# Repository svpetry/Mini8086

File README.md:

# Mini8086
A small, extensible Intel 8086 based computer system.

## PCBs

Some boards are made with Eagle but then I switched to KiCad because my Eagle License covers only 2 layer boards and I don't like their new licensing model (it's too expensive for hobbyists).
Schematics and layout are contained in the folders Eagle and KiCad.

### Backplane (Eagle)

First revision of the system backplane with 6 slots and a power connector.

### Backplane (KiCad)

Second revision of the backplane. Has 7 slots and two power connectors (one of them USB-C).

### RAM board (Eagle)

RAM board with 512 KB SRAM.

### Info board (KiCad)

A 16x2 HD44780 based LCD can be mounted to this board. Also contains some LEDs for important signals.

### LED board (KiCad)

Information board with LEDs for the busses and all important signals.

### CPU board Rev 1 (KiCad, "main") 

First revision of the CPU board, contains socket for an Intel 8086 CPU, ROM and other important system chips:
* Intel 8259 interrupt controller
* Intel 8254 timer

### CPU board Rev 2 (KiCad, "mainv2")

Second revision of the CPU board where I replaced most of the logic chips with an Altera CPLD. Also contains 1 MB SRAM so the external RAM board is not needed.

### VGA board (KiCad)

Simple graphics card with 128 KB SRAM and VGA output. Supported modes:
* text mode 80x25 characters, 256 colors (resolution 640x400 pixels)
* 320x200, 256 colors
* 320x400, 256 colors
* 640x200, 256 colors

### I/O board (KiCad)

* Slots for SD and MicroSD cards. Simple SPI controller implemented in an Altera CPLD.
* PS/2 keyboard connector
* RS232 connector
* I²C controller with a RTC module, BMP sensor module and EEPROM connected.

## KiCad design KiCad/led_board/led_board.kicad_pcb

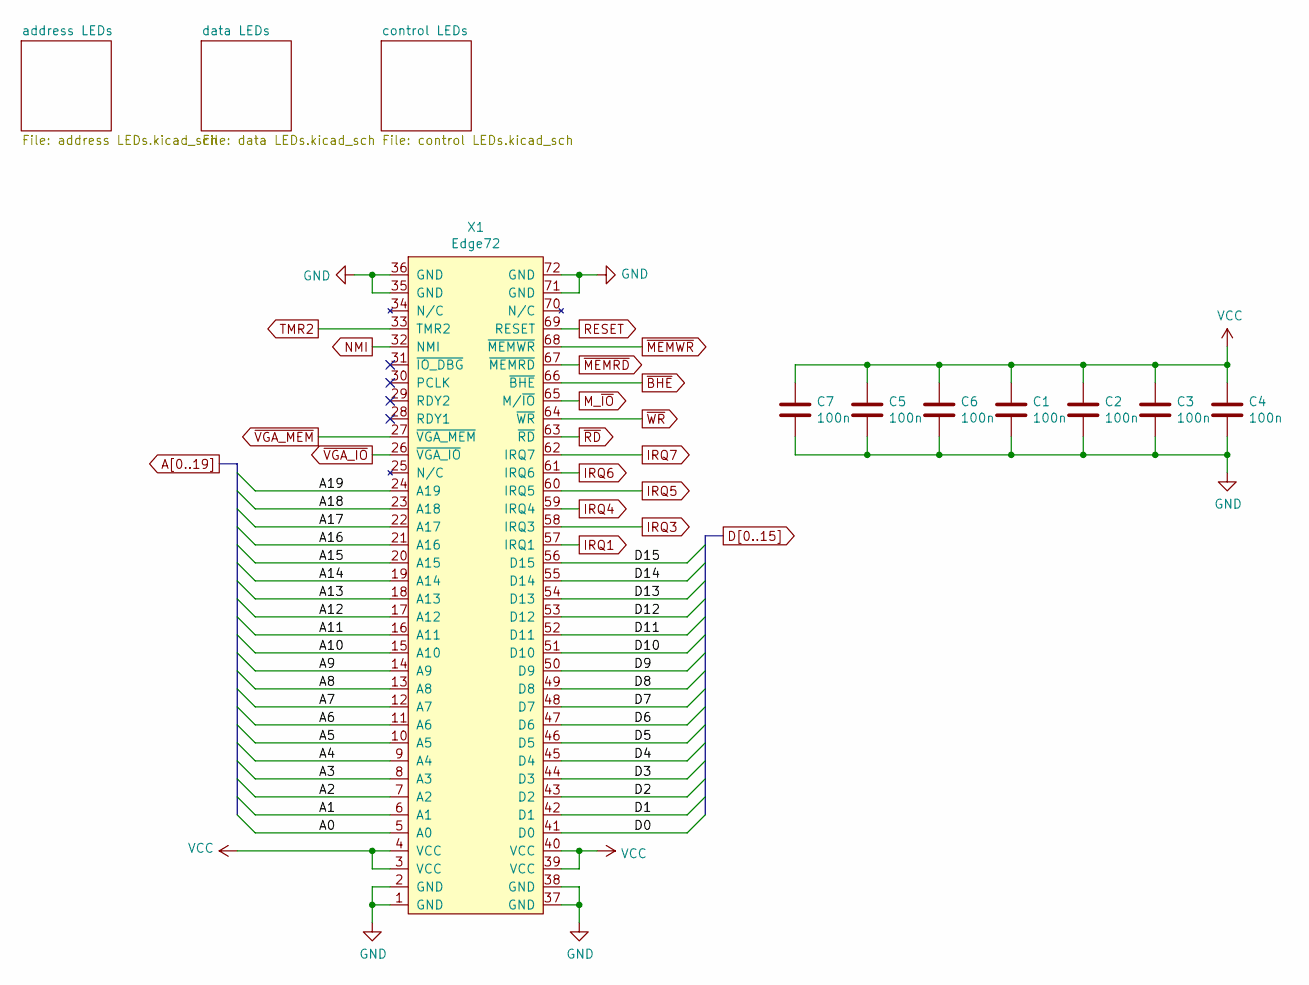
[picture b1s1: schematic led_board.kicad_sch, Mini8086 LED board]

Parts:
C1, C2, C3, C4, C5, C6, C7: 100n; C_1206_3216Metric; LCSC C24497
X1: Edge72; BUS_72

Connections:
A0: X1.5 (A0); also elsewhere on the board
A1: X1.6 (A1); also elsewhere on the board
A2: X1.7 (A2); also elsewhere on the board
A3: X1.8 (A3); also elsewhere on the board
A4: X1.9 (A4); also elsewhere on the board
A5: X1.10 (A5); also elsewhere on the board
A6: X1.11 (A6); also elsewhere on the board
A7: X1.12 (A7); also elsewhere on the board
A8: X1.13 (A8); also elsewhere on the board
A9: X1.14 (A9); also elsewhere on the board
A10: X1.15 (A10); also elsewhere on the board
A11: X1.16 (A11); also elsewhere on the board
A12: X1.17 (A12); also elsewhere on the board
A13: X1.18 (A13); also elsewhere on the board
A14: X1.19 (A14); also elsewhere on the board
A15: X1.20 (A15); also elsewhere on the board
A16: X1.21 (A16); also elsewhere on the board
A17: X1.22 (A17); also elsewhere on the board
A18: X1.23 (A18); also elsewhere on the board
A19: X1.24 (A19); also elsewhere on the board
D0: X1.41 (D0); also elsewhere on the board
D1: X1.42 (D1); also elsewhere on the board
D2: X1.43 (D2); also elsewhere on the board
D3: X1.44 (D3); also elsewhere on the board
D4: X1.45 (D4); also elsewhere on the board
D5: X1.46 (D5); also elsewhere on the board
D6: X1.47 (D6); also elsewhere on the board
D7: X1.48 (D7); also elsewhere on the board
D8: X1.49 (D8); also elsewhere on the board
D9: X1.50 (D9); also elsewhere on the board
D10: X1.51 (D10); also elsewhere on the board
D11: X1.52 (D11); also elsewhere on the board
D12: X1.53 (D12); also elsewhere on the board
D13: X1.54 (D13); also elsewhere on the board
D14: X1.55 (D14); also elsewhere on the board
D15: X1.56 (D15); also elsewhere on the board
GND: C1.2, C2.2, C3.2, C4.2, C5.2, C6.2, C7.2, X1.1 (GND), X1.2 (GND), X1.35 (GND), X1.36 (GND), X1.37 (GND), X1.38 (GND), X1.71 (GND), X1.72 (GND); also elsewhere on the board
IRQ1: X1.57 (IRQ1); also elsewhere on the board
IRQ3: X1.58 (IRQ3); also elsewhere on the board
IRQ4: X1.59 (IRQ4); also elsewhere on the board
IRQ5: X1.60 (IRQ5); also elsewhere on the board
IRQ6: X1.61 (IRQ6); also elsewhere on the board
IRQ7: X1.62 (IRQ7); also elsewhere on the board
M_~IO: X1.65 (M/~IO); also elsewhere on the board
NMI: X1.32 (NMI); also elsewhere on the board
RESET: X1.69 (RESET); also elsewhere on the board
TMR2: X1.33 (TMR2); also elsewhere on the board
VCC: C1.1, C2.1, C3.1, C4.1, C5.1, C6.1, C7.1, X1.3 (VCC), X1.4 (VCC), X1.39 (VCC), X1.40 (VCC); also elsewhere on the board
~BHE: X1.66 (~BHE); also elsewhere on the board
~MEMRD: X1.67 (~MEMRD); also elsewhere on the board
~MEMWR: X1.68 (~MEMWR); also elsewhere on the board
~RD: X1.63 (~RD); also elsewhere on the board
~VGA_IO: X1.26 (~VGA_IO); also elsewhere on the board
~VGA_MEM: X1.27 (~VGA_MEM); also elsewhere on the board
~WR: X1.64 (~WR); also elsewhere on the board

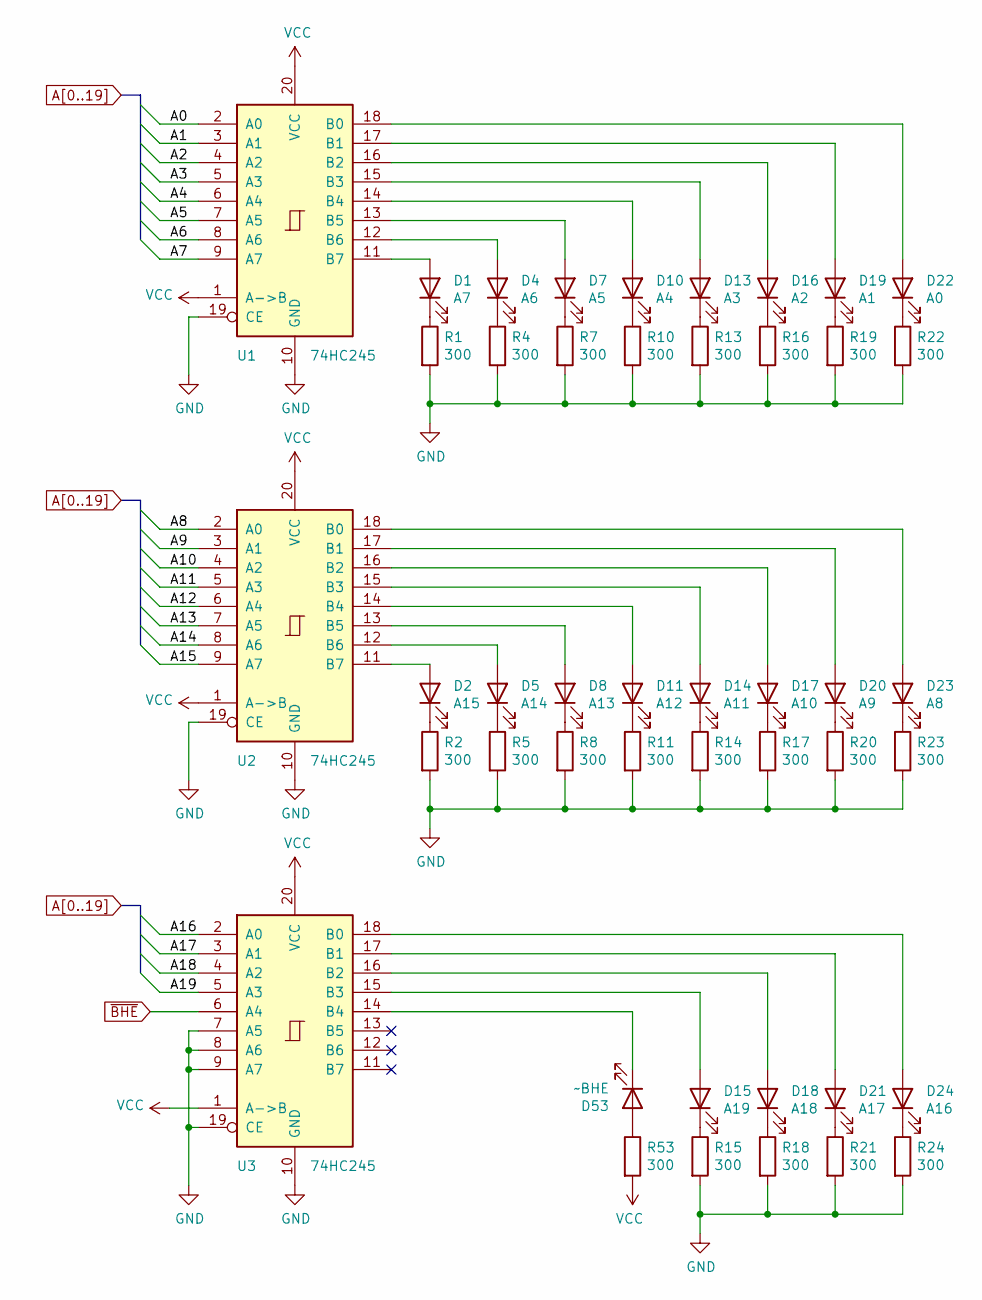
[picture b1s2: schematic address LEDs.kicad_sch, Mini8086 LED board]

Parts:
D1: A7; LED_0603_1608Metric
D2: A15; LED_0603_1608Metric
D4: A6; LED_0603_1608Metric
D5: A14; LED_0603_1608Metric
D7: A5; LED_0603_1608Metric
D8: A13; LED_0603_1608Metric
D10: A4; LED_0603_1608Metric
D11: A12; LED_0603_1608Metric
D13: A3; LED_0603_1608Metric
D14: A11; LED_0603_1608Metric
D15: A19; LED_0603_1608Metric
D16: A2; LED_0603_1608Metric
D17: A10; LED_0603_1608Metric
D18: A18; LED_0603_1608Metric
D19: A1; LED_0603_1608Metric
D20: A9; LED_0603_1608Metric
D21: A17; LED_0603_1608Metric
D22: A0; LED_0603_1608Metric
D23: A8; LED_0603_1608Metric
D24: A16; LED_0603_1608Metric
D53: ~BHE; LED_0603_1608Metric
R1, R2, R4, R5, R7, R8, R10, R11, R13, R14, R15, R16, R17, R18, R19, R20, R21, R22, R23, R24, R53: 300; R_1206_3216Metric
U1, U2, U3: 74HC245; SO-20_12.8x7.5mm_P1.27mm; LCSC C5625

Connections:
A0: U1.2 (A0); also elsewhere on the board
A1: U1.3 (A1); also elsewhere on the board
A2: U1.4 (A2); also elsewhere on the board
A3: U1.5 (A3); also elsewhere on the board
A4: U1.6 (A4); also elsewhere on the board
A5: U1.7 (A5); also elsewhere on the board
A6: U1.8 (A6); also elsewhere on the board
A7: U1.9 (A7); also elsewhere on the board
A8: U2.2 (A0); also elsewhere on the board
A9: U2.3 (A1); also elsewhere on the board
A10: U2.4 (A2); also elsewhere on the board
A11: U2.5 (A3); also elsewhere on the board
A12: U2.6 (A4); also elsewhere on the board
A13: U2.7 (A5); also elsewhere on the board
A14: U2.8 (A6); also elsewhere on the board
A15: U2.9 (A7); also elsewhere on the board
A16: U3.2 (A0); also elsewhere on the board
A17: U3.3 (A1); also elsewhere on the board
A18: U3.4 (A2); also elsewhere on the board
A19: U3.5 (A3); also elsewhere on the board
GND: R1.2, R2.2, R4.2, R5.2, R7.2, R8.2, R10.2, R11.2, R13.2, R14.2, R15.2, R16.2, R17.2, R18.2, R19.2, R20.2, R21.2, R22.2, R23.2, R24.2, U1.10 (GND), U1.19 (CE), U2.10 (GND), U2.19 (CE), U3.7 (A5), U3.8 (A6), U3.9 (A7), U3.10 (GND), U3.19 (CE); also elsewhere on the board
unnamed: D1.2 (A), U1.11 (B7)
unnamed: D1.1 (K), R1.1
unnamed: D2.2 (A), U2.11 (B7)
unnamed: D2.1 (K), R2.1
unnamed: D4.2 (A), U1.12 (B6)
unnamed: D4.1 (K), R4.1
unnamed: D5.2 (A), U2.12 (B6)
unnamed: D5.1 (K), R5.1
unnamed: D7.2 (A), U1.13 (B5)
unnamed: D7.1 (K), R7.1
unnamed: D8.2 (A), U2.13 (B5)
unnamed: D8.1 (K), R8.1
unnamed: D10.2 (A), U1.14 (B4)
unnamed: D10.1 (K), R10.1
unnamed: D11.2 (A), U2.14 (B4)
unnamed: D11.1 (K), R11.1
unnamed: D13.2 (A), U1.15 (B3)
unnamed: D13.1 (K), R13.1
unnamed: D14.2 (A), U2.15 (B3)
unnamed: D14.1 (K), R14.1
unnamed: D15.2 (A), U3.15 (B3)
unnamed: D15.1 (K), R15.1
unnamed: D16.2 (A), U1.16 (B2)
unnamed: D16.1 (K), R16.1
unnamed: D17.2 (A), U2.16 (B2)
unnamed: D17.1 (K), R17.1
unnamed: D18.2 (A), U3.16 (B2)
unnamed: D18.1 (K), R18.1
unnamed: D19.2 (A), U1.17 (B1)
unnamed: D19.1 (K), R19.1
unnamed: D20.2 (A), U2.17 (B1)
unnamed: D20.1 (K), R20.1
unnamed: D21.2 (A), U3.17 (B1)
unnamed: D21.1 (K), R21.1
unnamed: D22.2 (A), U1.18 (B0)
unnamed: D22.1 (K), R22.1
unnamed: D23.2 (A), U2.18 (B0)
unnamed: D23.1 (K), R23.1
unnamed: D24.2 (A), U3.18 (B0)
unnamed: D24.1 (K), R24.1
unnamed: D53.2 (A), R53.1
unnamed: D53.1 (K), U3.14 (B4)
VCC: R53.2, U1.1 (A->B), U1.20 (VCC), U2.1 (A->B), U2.20 (VCC), U3.1 (A->B), U3.20 (VCC); also elsewhere on the board
~BHE: U3.6 (A4); also elsewhere on the board

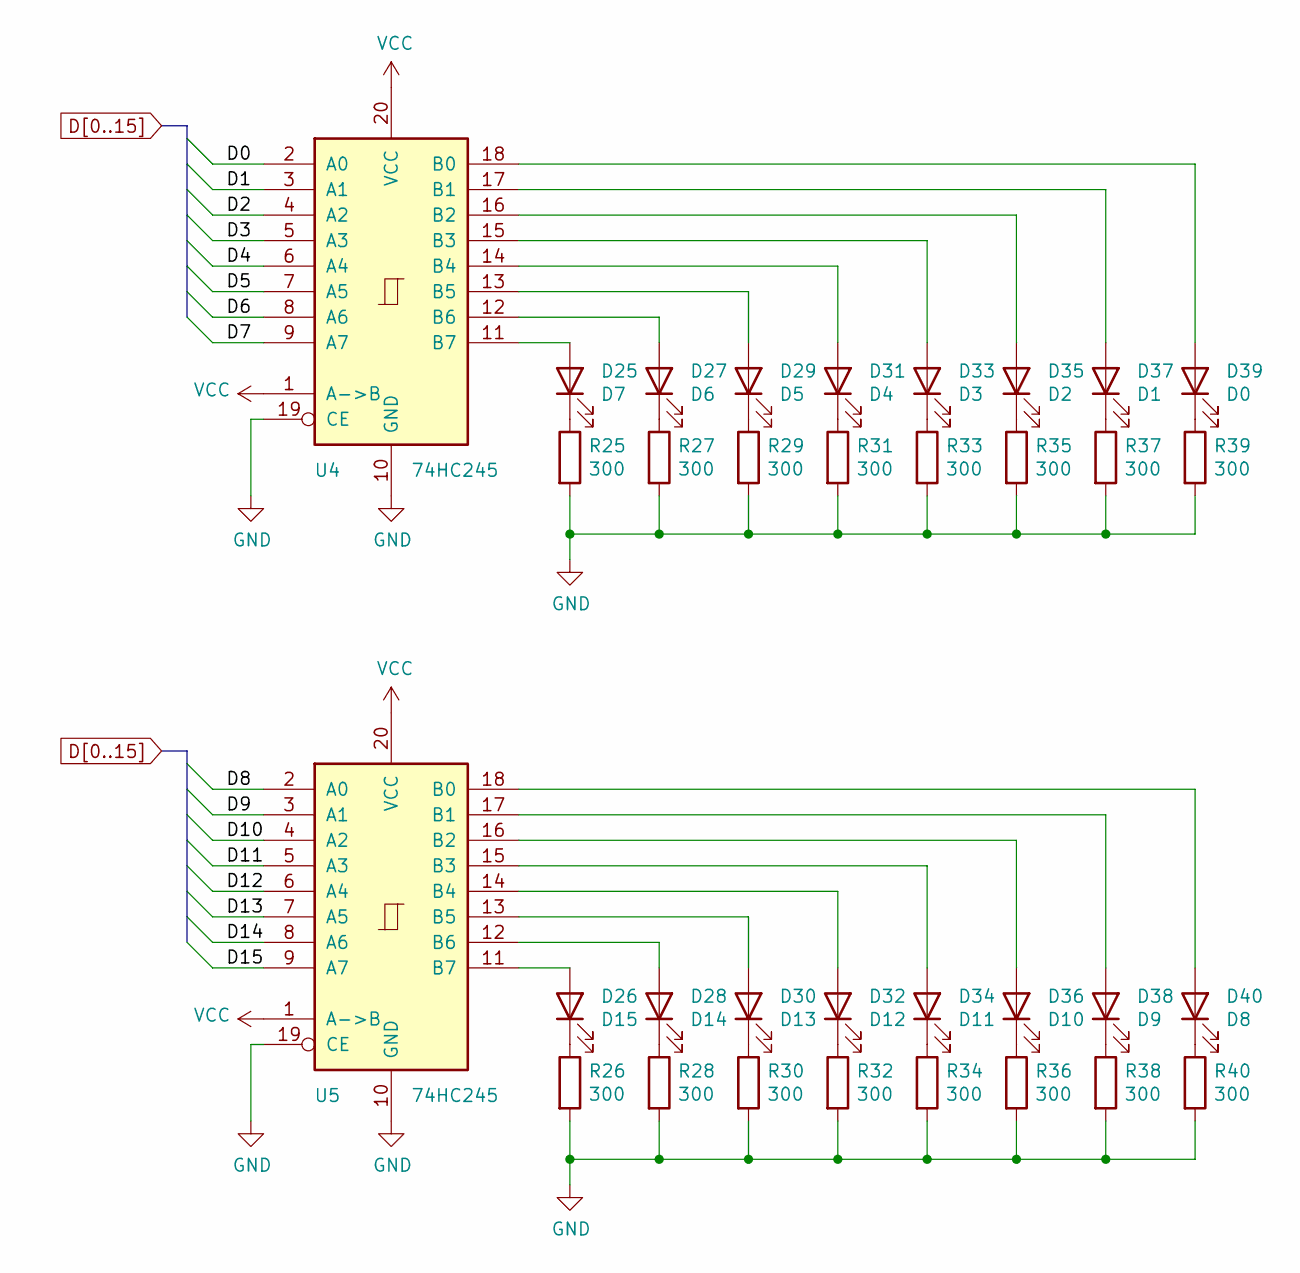
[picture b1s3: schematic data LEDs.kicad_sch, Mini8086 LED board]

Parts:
D25: D7; LED_0603_1608Metric
D26: D15; LED_0603_1608Metric
D27: D6; LED_0603_1608Metric
D28: D14; LED_0603_1608Metric
D29: D5; LED_0603_1608Metric
D30: D13; LED_0603_1608Metric
D31: D4; LED_0603_1608Metric
D32: D12; LED_0603_1608Metric
D33: D3; LED_0603_1608Metric
D34: D11; LED_0603_1608Metric
D35: D2; LED_0603_1608Metric
D36: D10; LED_0603_1608Metric
D37: D1; LED_0603_1608Metric
D38: D9; LED_0603_1608Metric
D39: D0; LED_0603_1608Metric
D40: D8; LED_0603_1608Metric
R25, R26, R27, R28, R29, R30, R31, R32, R33, R34, R35, R36, R37, R38, R39, R40: 300; R_1206_3216Metric
U4, U5: 74HC245; SO-20_12.8x7.5mm_P1.27mm; LCSC C5625

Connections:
D0: U4.2 (A0); also elsewhere on the board
D1: U4.3 (A1); also elsewhere on the board
D2: U4.4 (A2); also elsewhere on the board
D3: U4.5 (A3); also elsewhere on the board
D4: U4.6 (A4); also elsewhere on the board
D5: U4.7 (A5); also elsewhere on the board
D6: U4.8 (A6); also elsewhere on the board
D7: U4.9 (A7); also elsewhere on the board
D8: U5.2 (A0); also elsewhere on the board
D9: U5.3 (A1); also elsewhere on the board
D10: U5.4 (A2); also elsewhere on the board
D11: U5.5 (A3); also elsewhere on the board
D12: U5.6 (A4); also elsewhere on the board
D13: U5.7 (A5); also elsewhere on the board
D14: U5.8 (A6); also elsewhere on the board
D15: U5.9 (A7); also elsewhere on the board
GND: R25.2, R26.2, R27.2, R28.2, R29.2, R30.2, R31.2, R32.2, R33.2, R34.2, R35.2, R36.2, R37.2, R38.2, R39.2, R40.2, U4.10 (GND), U4.19 (CE), U5.10 (GND), U5.19 (CE); also elsewhere on the board
unnamed: D25.2 (A), U4.11 (B7)
unnamed: D25.1 (K), R25.1
unnamed: D26.2 (A), U5.11 (B7)
unnamed: D26.1 (K), R26.1
unnamed: D27.2 (A), U4.12 (B6)
unnamed: D27.1 (K), R27.1
unnamed: D28.2 (A), U5.12 (B6)
unnamed: D28.1 (K), R28.1
unnamed: D29.2 (A), U4.13 (B5)
unnamed: D29.1 (K), R29.1
unnamed: D30.2 (A), U5.13 (B5)
unnamed: D30.1 (K), R30.1
unnamed: D31.2 (A), U4.14 (B4)
unnamed: D31.1 (K), R31.1
unnamed: D32.2 (A), U5.14 (B4)
unnamed: D32.1 (K), R32.1
unnamed: D33.2 (A), U4.15 (B3)
unnamed: D33.1 (K), R33.1
unnamed: D34.2 (A), U5.15 (B3)
unnamed: D34.1 (K), R34.1
unnamed: D35.2 (A), U4.16 (B2)
unnamed: D35.1 (K), R35.1
unnamed: D36.2 (A), U5.16 (B2)
unnamed: D36.1 (K), R36.1
unnamed: D37.2 (A), U4.17 (B1)
unnamed: D37.1 (K), R37.1
unnamed: D38.2 (A), U5.17 (B1)
unnamed: D38.1 (K), R38.1
unnamed: D39.2 (A), U4.18 (B0)
unnamed: D39.1 (K), R39.1
unnamed: D40.2 (A), U5.18 (B0)
unnamed: D40.1 (K), R40.1
VCC: U4.1 (A->B), U4.20 (VCC), U5.1 (A->B), U5.20 (VCC); also elsewhere on the board

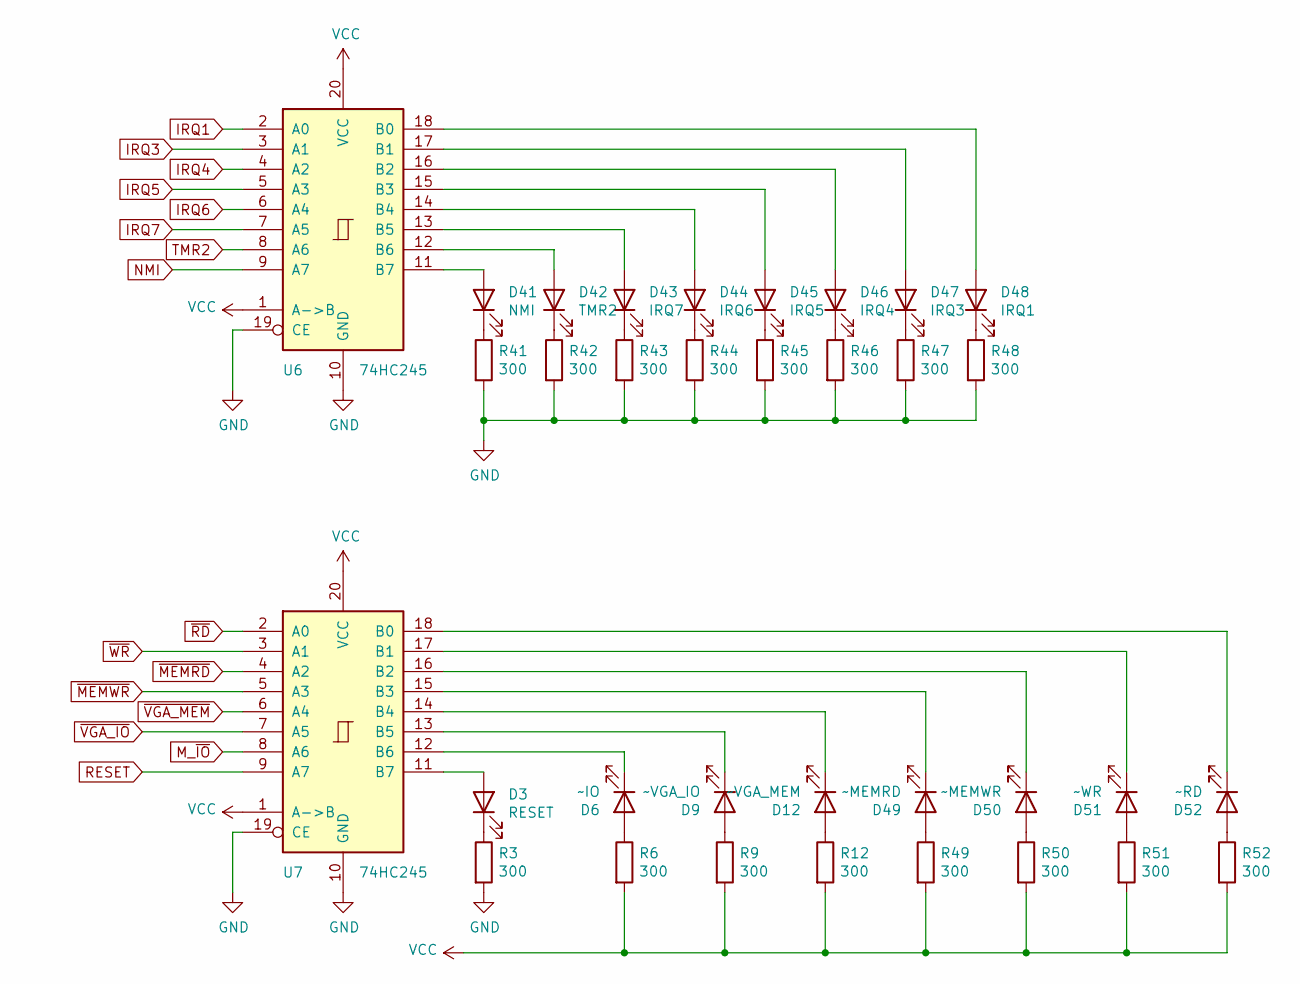
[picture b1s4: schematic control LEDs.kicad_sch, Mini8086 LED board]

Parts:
D3: RESET; LED_0603_1608Metric
D6: ~IO; LED_0603_1608Metric
D9: ~VGA_IO; LED_0603_1608Metric
D12: ~VGA_MEM; LED_0603_1608Metric
D41: NMI; LED_0603_1608Metric
D42: TMR2; LED_0603_1608Metric
D43: IRQ7; LED_0603_1608Metric
D44: IRQ6; LED_0603_1608Metric
D45: IRQ5; LED_0603_1608Metric
D46: IRQ4; LED_0603_1608Metric
D47: IRQ3; LED_0603_1608Metric
D48: IRQ1; LED_0603_1608Metric
D49: ~MEMRD; LED_0603_1608Metric
D50: ~MEMWR; LED_0603_1608Metric
D51: ~WR; LED_0603_1608Metric
D52: ~RD; LED_0603_1608Metric
R3, R6, R9, R12, R41, R42, R43, R44, R45, R46, R47, R48, R49, R50, R51, R52: 300; R_1206_3216Metric; LCSC C17887
U6, U7: 74HC245; SO-20_12.8x7.5mm_P1.27mm; LCSC C5625

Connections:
GND: R3.2, R41.2, R42.2, R43.2, R44.2, R45.2, R46.2, R47.2, R48.2, U6.10 (GND), U6.19 (CE), U7.10 (GND), U7.19 (CE); also elsewhere on the board
IRQ1: U6.2 (A0); also elsewhere on the board
IRQ3: U6.3 (A1); also elsewhere on the board
IRQ4: U6.4 (A2); also elsewhere on the board
IRQ5: U6.5 (A3); also elsewhere on the board
IRQ6: U6.6 (A4); also elsewhere on the board
IRQ7: U6.7 (A5); also elsewhere on the board
M_~IO: U7.8 (A6); also elsewhere on the board
NMI: U6.9 (A7); also elsewhere on the board
unnamed: D3.2 (A), U7.11 (B7)
unnamed: D3.1 (K), R3.1
unnamed: D6.2 (A), R6.1
unnamed: D6.1 (K), U7.12 (B6)
unnamed: D9.2 (A), R9.1
unnamed: D9.1 (K), U7.13 (B5)
unnamed: D12.2 (A), R12.1
unnamed: D12.1 (K), U7.14 (B4)
unnamed: D41.2 (A), U6.11 (B7)
unnamed: D41.1 (K), R41.1
unnamed: D42.2 (A), U6.12 (B6)
unnamed: D42.1 (K), R42.1
unnamed: D43.2 (A), U6.13 (B5)
unnamed: D43.1 (K), R43.1
unnamed: D44.2 (A), U6.14 (B4)
unnamed: D44.1 (K), R44.1
unnamed: D45.2 (A), U6.15 (B3)
unnamed: D45.1 (K), R45.1
unnamed: D46.2 (A), U6.16 (B2)
unnamed: D46.1 (K), R46.1
unnamed: D47.2 (A), U6.17 (B1)
unnamed: D47.1 (K), R47.1
unnamed: D48.2 (A), U6.18 (B0)
unnamed: D48.1 (K), R48.1
unnamed: D49.2 (A), R49.1
unnamed: D49.1 (K), U7.15 (B3)
unnamed: D50.2 (A), R50.1
unnamed: D50.1 (K), U7.16 (B2)
unnamed: D51.2 (A), R51.1
unnamed: D51.1 (K), U7.17 (B1)
unnamed: D52.2 (A), R52.1
unnamed: D52.1 (K), U7.18 (B0)
RESET: U7.9 (A7); also elsewhere on the board
TMR2: U6.8 (A6); also elsewhere on the board
VCC: R6.2, R9.2, R12.2, R49.2, R50.2, R51.2, R52.2, U6.1 (A->B), U6.20 (VCC), U7.1 (A->B), U7.20 (VCC); also elsewhere on the board
~MEMRD: U7.4 (A2); also elsewhere on the board
~MEMWR: U7.5 (A3); also elsewhere on the board
~RD: U7.2 (A0); also elsewhere on the board
~VGA_IO: U7.7 (A5); also elsewhere on the board
~VGA_MEM: U7.6 (A4); also elsewhere on the board
~WR: U7.3 (A1); also elsewhere on the board

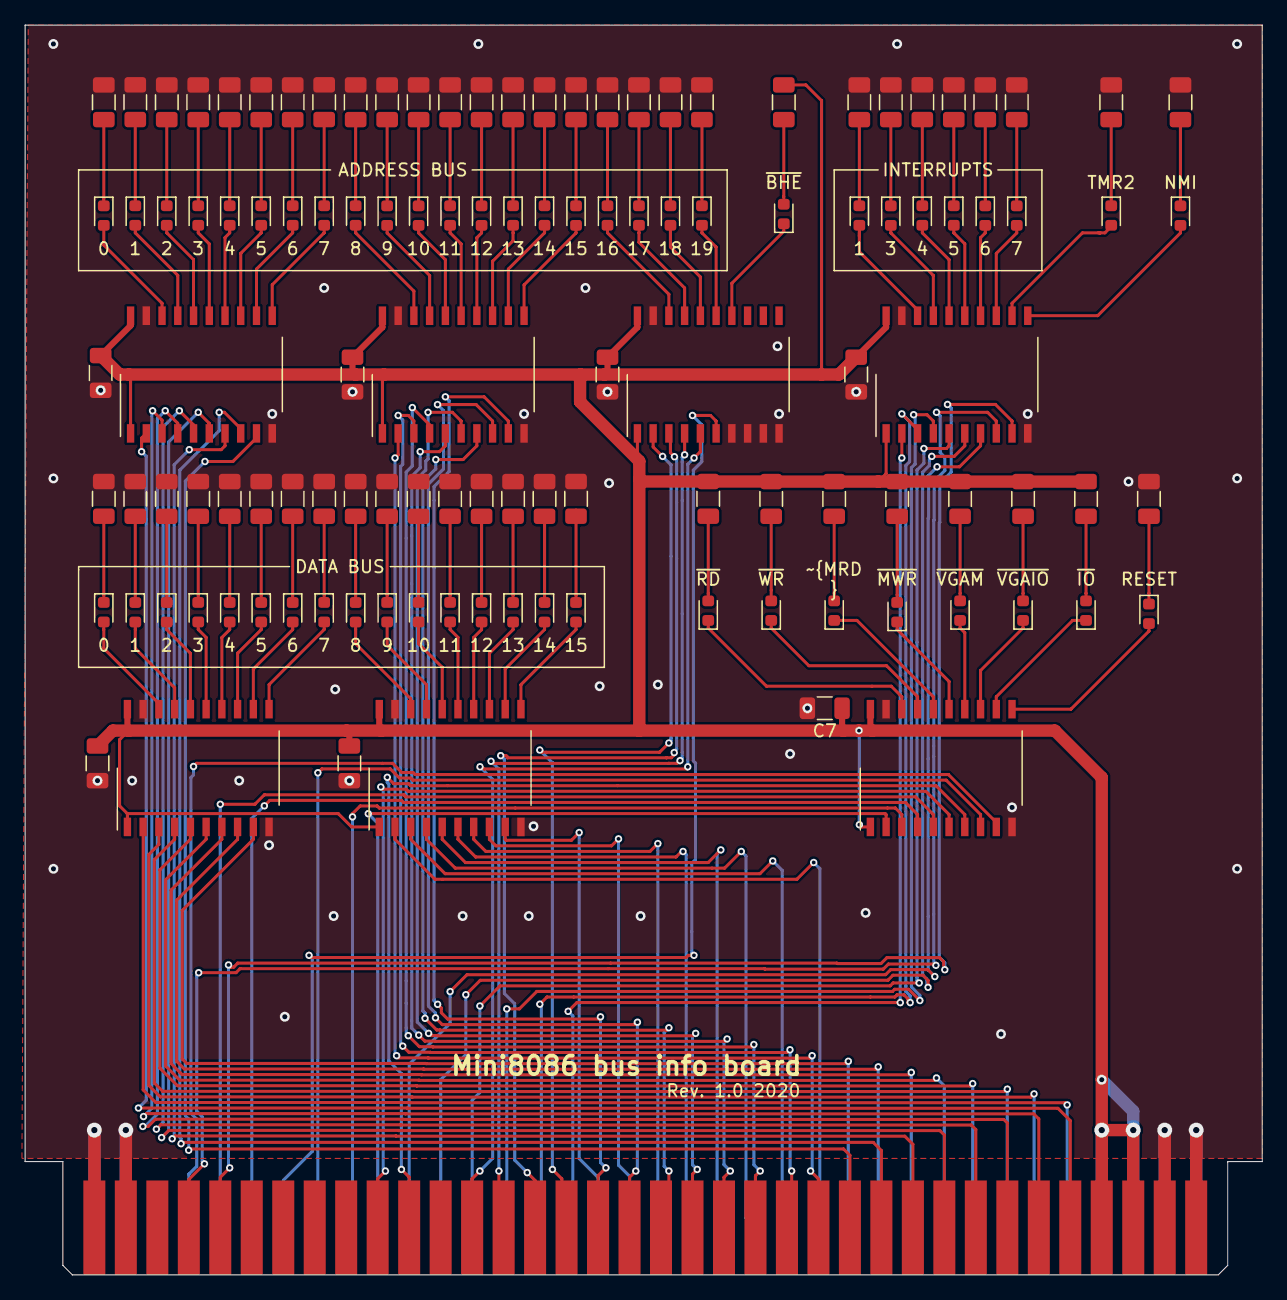
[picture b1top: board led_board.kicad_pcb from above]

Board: 2 copper layers, 99.8 x 100.8 mm, 121 parts (0 on the bottom side), 161 nets.

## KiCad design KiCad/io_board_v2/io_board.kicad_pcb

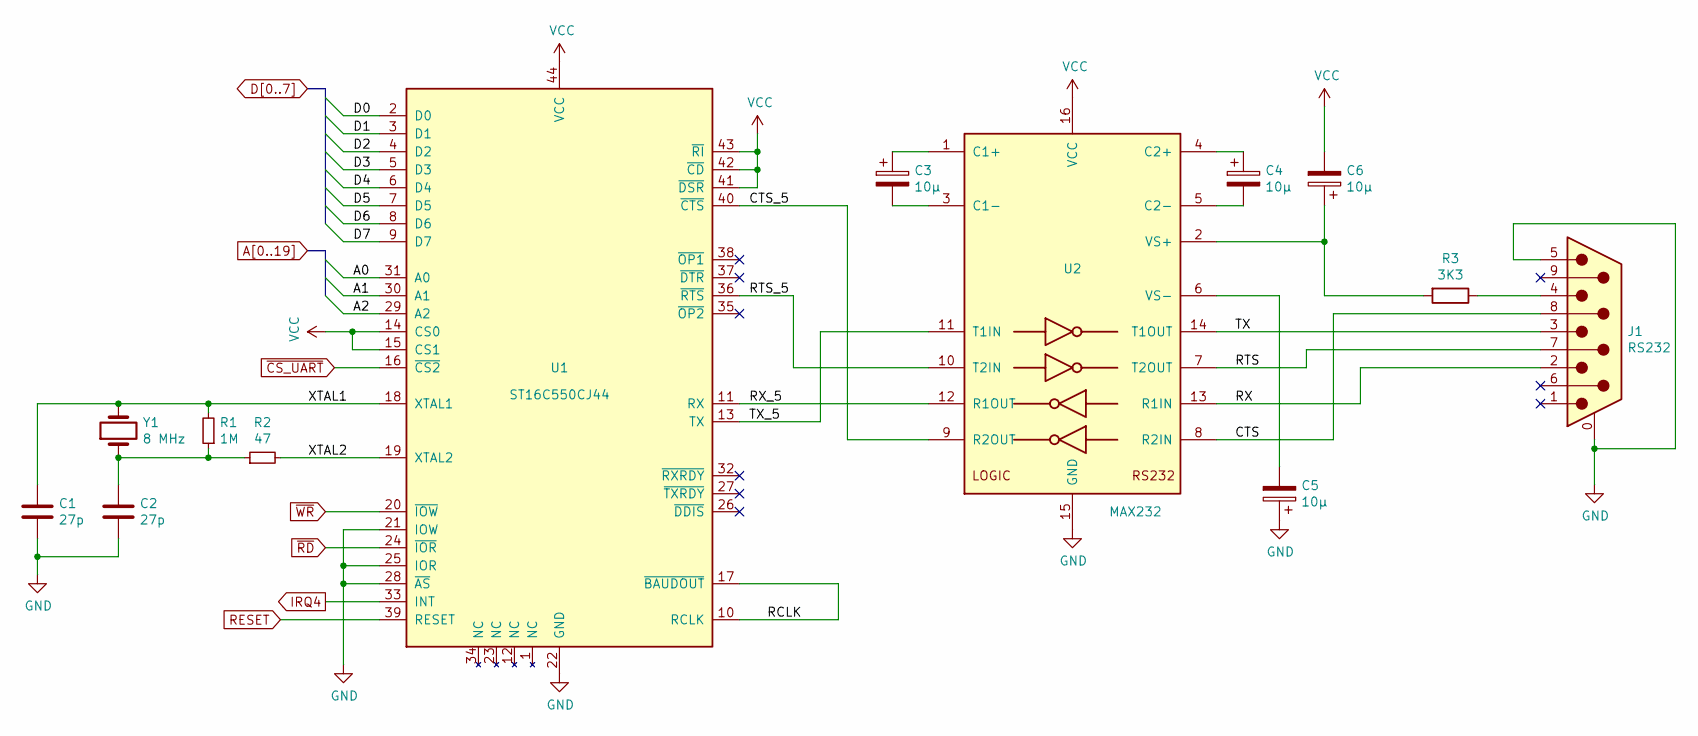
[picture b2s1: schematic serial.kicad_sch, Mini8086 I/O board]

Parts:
C1, C2: 27p; C_1206_3216Metric
C3, C4, C5, C6: 10µ; CP_Elec_4x3.9
J1: RS232; DSUB-9_Male_Horizontal_P2.77x2.84mm_EdgePinOffset4.94mm_Hou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
R1: 1M; R_1206_3216Metric
R2: 47; R_1206_3216Metric
R3: 3K3; R_1206_3216Metric
U1: ST16C550CJ44; PLCC-44_THT-Socket
U2: MAX232; SOIC-16_3.9x9.9mm_P1.27mm
Y1: 8 MHz; Crystal_HC49-U_Vertical

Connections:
/serial/CTS: J1.8, U2.8 (R2IN)
/serial/CTS_5: U1.40 (~CTS), U2.9 (R2OUT)
/serial/RCLK: U1.10 (RCLK), U1.17 (~BAUDOUT)
/serial/RTS: J1.7, U2.7 (T2OUT)
/serial/RTS_5: U1.36 (~RTS), U2.10 (T2IN)
/serial/RX: J1.2, U2.13 (R1IN)
/serial/RX_5: U1.11 (RX), U2.12 (R1OUT)
/serial/TX: J1.3, U2.14 (T1OUT)
/serial/TX_5: U1.13 (TX), U2.11 (T1IN)
/serial/XTAL1: C1.1, R1.2, U1.18 (XTAL1), Y1.2
/serial/XTAL2: R2.2, U1.19 (XTAL2)
A0: U1.31 (A0); also elsewhere on the board
A1: U1.30 (A1); also elsewhere on the board
A2: U1.29 (A2); also elsewhere on the board
D0: U1.2 (D0); also elsewhere on the board
D1: U1.3 (D1); also elsewhere on the board
D2: U1.4 (D2); also elsewhere on the board
D3: U1.5 (D3); also elsewhere on the board
D4: U1.6 (D4); also elsewhere on the board
D5: U1.7 (D5); also elsewhere on the board
D6: U1.8 (D6); also elsewhere on the board
D7: U1.9 (D7); also elsewhere on the board
GND: C1.2, C2.2, C5.1, J1.0 (PAD), J1.5, U1.21 (IOW), U1.22 (GND), U1.25 (IOR), U1.28 (~AS), U2.15 (GND); also elsewhere on the board
IRQ4: U1.33 (INT); also elsewhere on the board
unnamed: C2.1, R1.1, R2.1, Y1.1
unnamed: J1.4, R3.1
unnamed: C3.1, U2.1 (C1+)
unnamed: C3.2, U2.3 (C1-)
unnamed: C4.1, U2.4 (C2+)
unnamed: C4.2, U2.5 (C2-)
unnamed: C6.1, R3.2, U2.2 (VS+)
unnamed: C5.2, U2.6 (VS-)
RESET: U1.39 (RESET); also elsewhere on the board
VCC: C6.2, U1.14 (CS0), U1.15 (CS1), U1.41 (~DSR), U1.42 (~CD), U1.43 (~RI), U1.44 (VCC), U2.16 (VCC); also elsewhere on the board
~CS_UART: U1.16 (~CS2); also elsewhere on the board
~RD: U1.24 (~IOR); also elsewhere on the board
~WR: U1.20 (~IOW); also elsewhere on the board

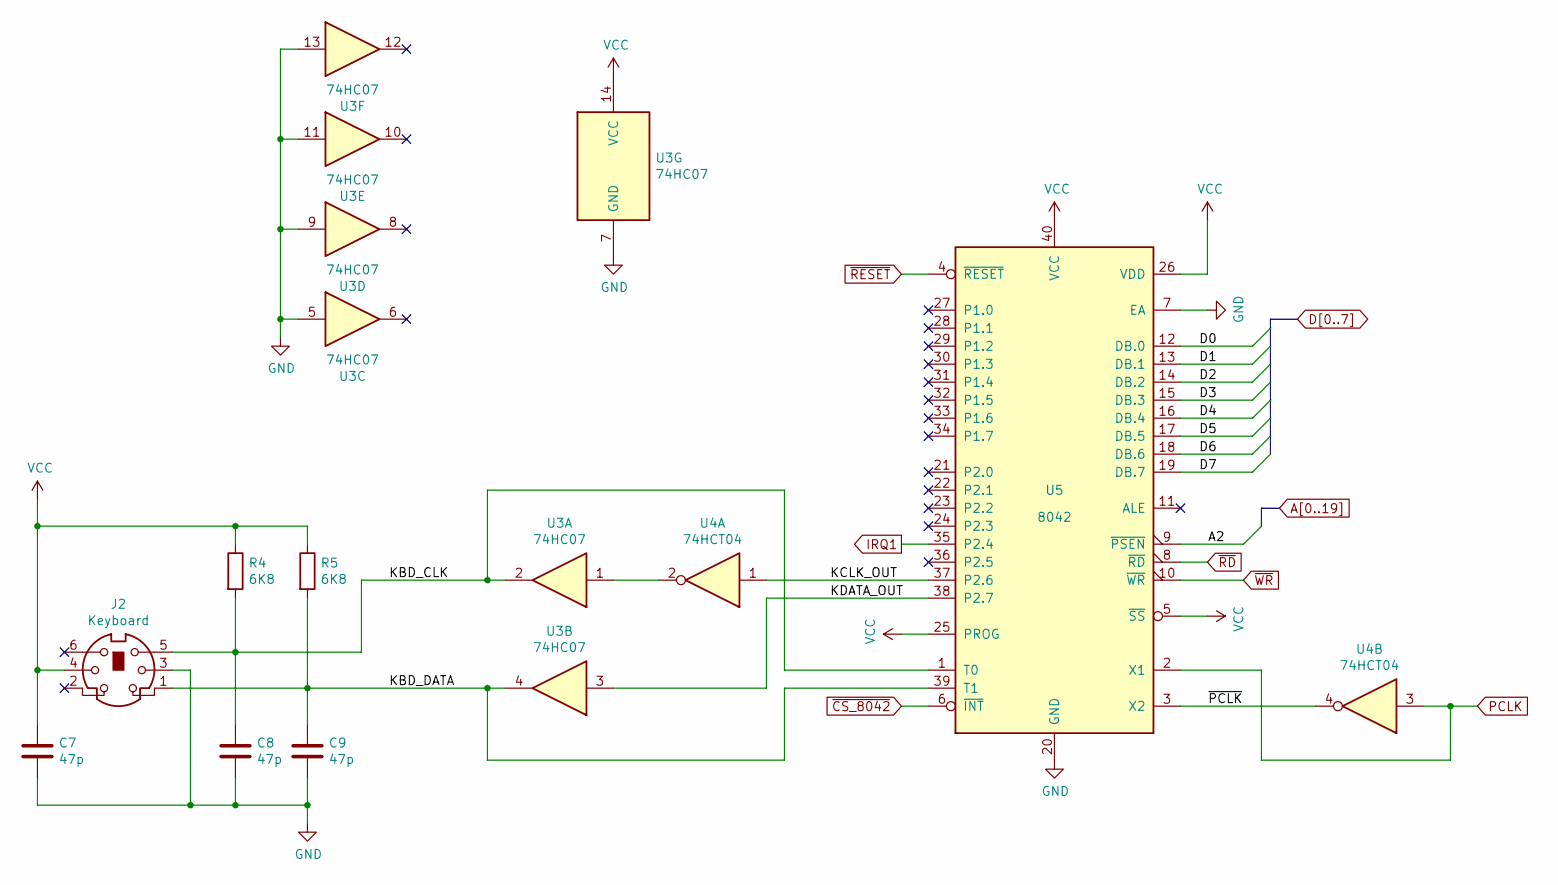
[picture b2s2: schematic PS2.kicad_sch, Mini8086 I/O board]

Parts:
C7, C8, C9: 47p; C_1206_3216Metric
J2: Keyboard; Mini_din6
R4, R5: 6K8; R_1206_3216Metric
U3: 74HC07; SOIC-14_3.9x8.7mm_P1.27mm
U4: 74HCT04; SOIC-14_3.9x8.7mm_P1.27mm
U5: 8042; DIP-40_W15.24mm_Socket_LongPads

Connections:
/PS2/KBD_CLK: C8.1, J2.5, R4.2, U3.2, U5.1 (T0)
/PS2/KBD_DATA: C9.1, J2.1, R5.2, U3.4, U5.39 (T1)
/PS2/KCLK_OUT: U4.1, U5.37 (P2.6)
/PS2/KDATA_OUT: U3.3, U5.38 (P2.7)
/PS2/~PCLK: U4.4, U5.3 (X2)
A2: U5.9 (~PSEN); also elsewhere on the board
D0: U5.12 (DB.0); also elsewhere on the board
D1: U5.13 (DB.1); also elsewhere on the board
D2: U5.14 (DB.2); also elsewhere on the board
D3: U5.15 (DB.3); also elsewhere on the board
D4: U5.16 (DB.4); also elsewhere on the board
D5: U5.17 (DB.5); also elsewhere on the board
D6: U5.18 (DB.6); also elsewhere on the board
D7: U5.19 (DB.7); also elsewhere on the board
GND: C7.2, C8.2, C9.2, J2.3, U3.5, U3.7 (GND), U3.9, U3.11, U3.13, U5.7 (EA), U5.20 (GND); also elsewhere on the board
IRQ1: U5.35 (P2.4); also elsewhere on the board
unnamed: U3.1, U4.2
PCLK: U4.3, U5.2 (X1); also elsewhere on the board
VCC: C7.1, J2.4, R4.1, R5.1, U3.14 (VCC), U5.5 (~SS), U5.25 (PROG), U5.26 (VDD), U5.40 (VCC); also elsewhere on the board
~CS_8042: U5.6 (~INT); also elsewhere on the board
~RD: U5.8 (~RD); also elsewhere on the board
~RESET: U5.4 (~RESET); also elsewhere on the board
~WR: U5.10 (~WR); also elsewhere on the board
